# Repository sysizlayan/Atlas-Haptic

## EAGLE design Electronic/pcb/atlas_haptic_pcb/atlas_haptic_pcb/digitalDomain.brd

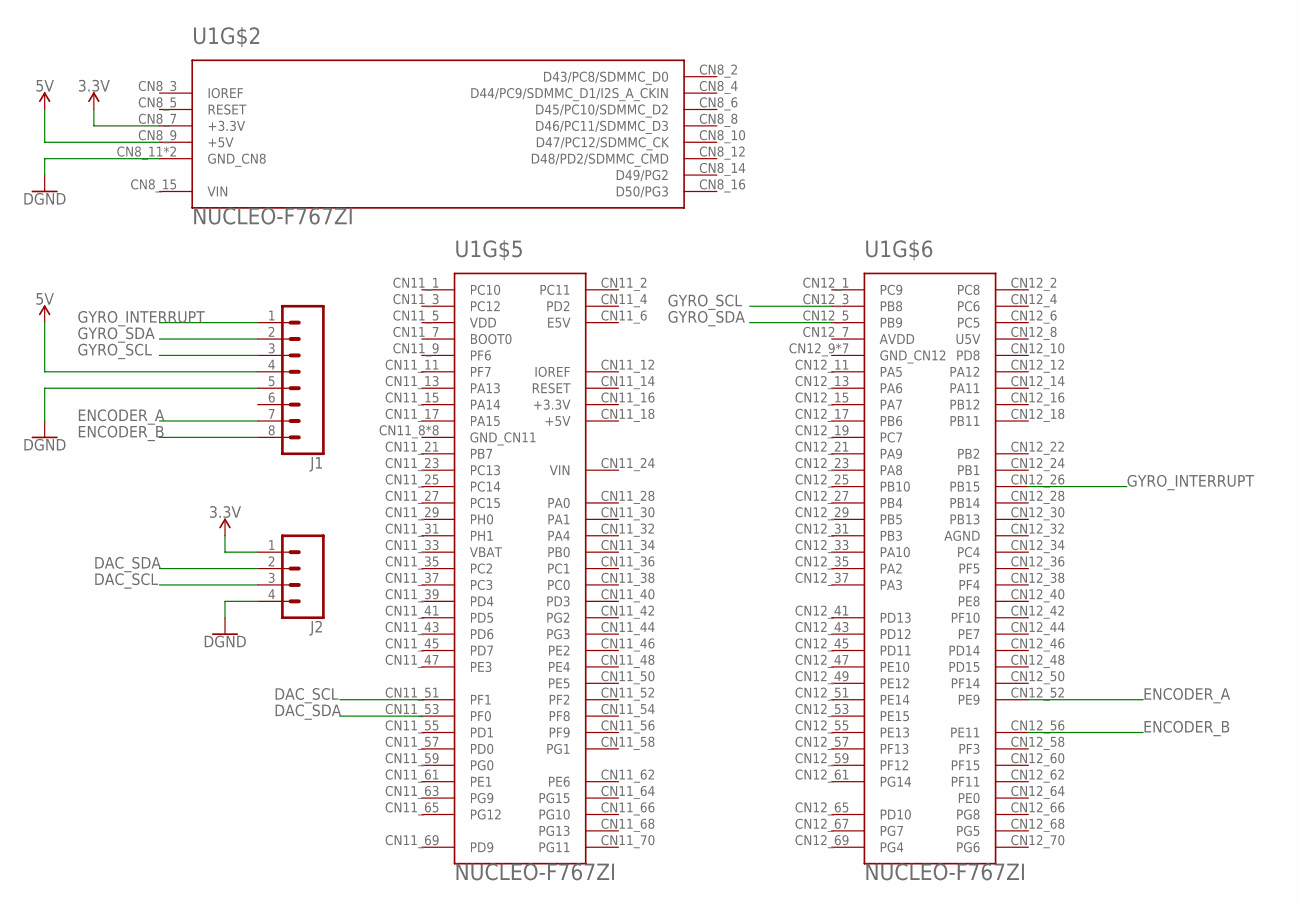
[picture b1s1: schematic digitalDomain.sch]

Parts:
J1: CONN_08LONGPADS; 1X08_LONGPADS
J2: CONN_04LONGPADS; 1X04_LONGPADS
U1: NUCLEO-F767ZI; MODULE_NUCLEO-F429ZI

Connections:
3.3V: J2.1, U1.CN8_7 (+3.3V)
5V: J1.4, U1.CN8_9 (+5V)
DAC_SCL: J2.3, U1.CN11_51 (PF1)
DAC_SDA: J2.2, U1.CN11_53 (PF0)
ENCODER_A: J1.7, U1.CN12_52 (PE9)
ENCODER_B: J1.8, U1.CN12_56 (PE11)
GND: J1.5, J2.4, U1.CN8_11 (GND_CN8), U1.CN8_13 (GND_CN8)
GYRO_INTERRUPT: J1.1, U1.CN12_26 (PB15)
GYRO_SCL: J1.3, U1.CN12_3 (PB8)
GYRO_SDA: J1.2, U1.CN12_5 (PB9)

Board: 2 copper layers, 3 parts (0 on the bottom side), 10 nets, no tracks yet.

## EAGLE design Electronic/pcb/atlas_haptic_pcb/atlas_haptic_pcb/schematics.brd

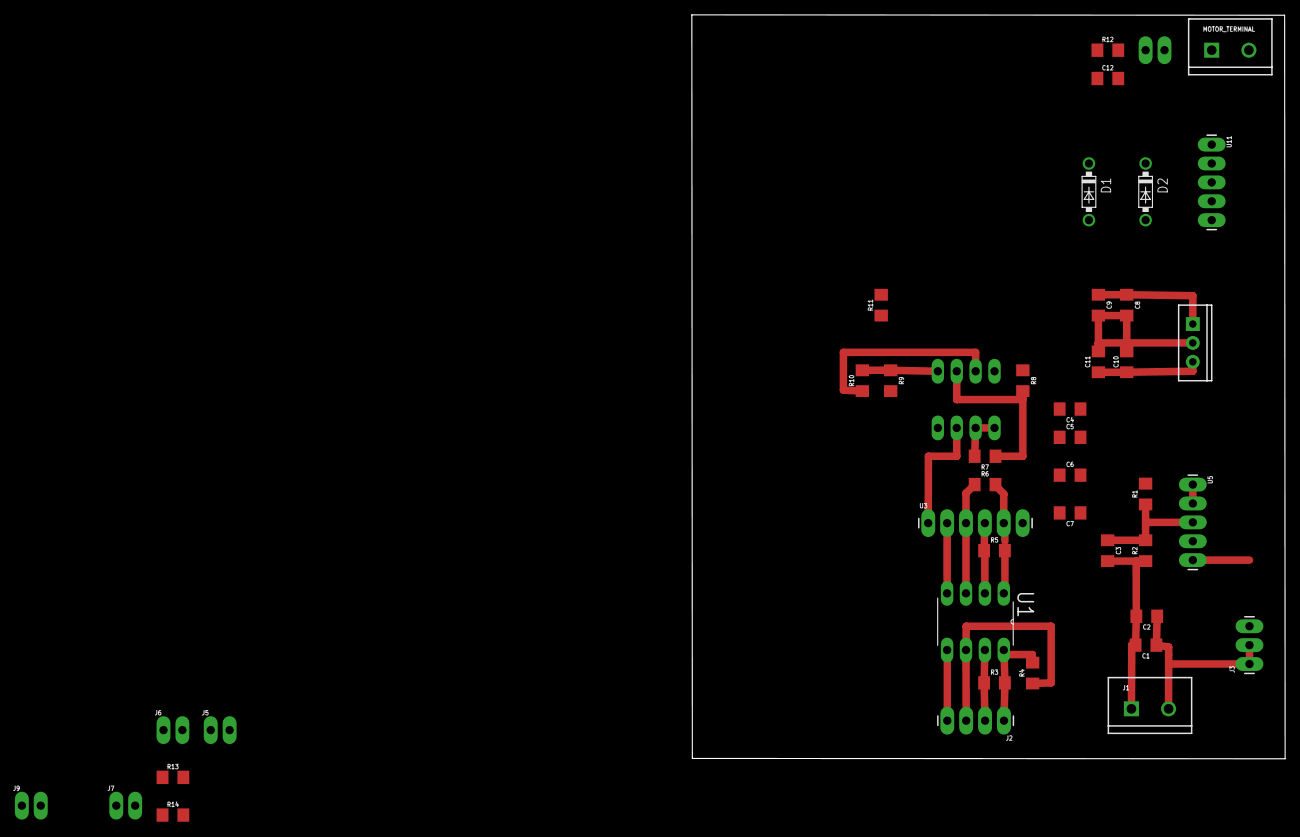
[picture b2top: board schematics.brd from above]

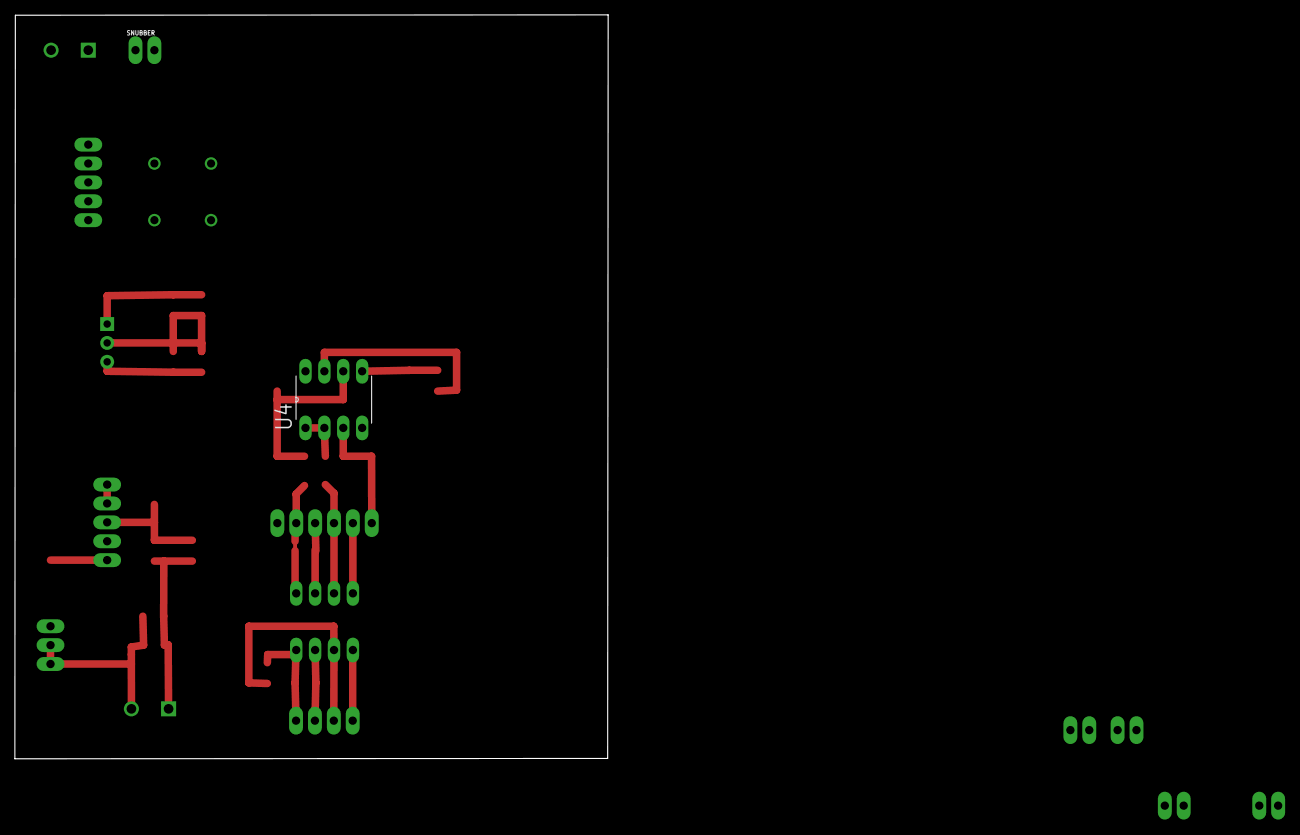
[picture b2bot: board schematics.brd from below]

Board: 2 copper layers, 79.8 x 100.0 mm, 43 parts (2 on the bottom side), 24 nets.

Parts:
C1, C8, C10: 1.0uF; 1206
C2, C3, C4, C6, C9, C11: 100nF; 1206
C5, C7: 1uF; 1206
C12: 1n; 1206
D1, D2: 1N5819-B; DO41-7.6
J1: SCREWTERMINAL-5MM-2
J2: 1X04_LONGPADS
J3: 1X03_LONGPADS
J5, J6, J7, J9: Jumper; 1X02_LONGPADS
MOTOR_TERMINAL: SCREWTERMINAL-5MM-2
R1, R2, R7: 1K; 1206
R3, R4, R5, R6: 1k; 1206
R8, R9, R10: 2K; 1206
R11: 0R01; 1206
R12: 10; 1206
R13: 0R1; 1206
R14: 1R0; 1206
SNUBBER: Jumper; 1X02_LONGPADS
U1: ISO1541; DIP254P762X508-8
U2: TO220-IGO
U3: MCP4725; 1X06_LONGPADS
U4: LM833N; DIP254P762X508-8
U5, U11: OPA549; 1X05_LONGPADS

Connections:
5V: C10.1, C11.1, R5.2, R6.2, R9.2, U1.1, U2.OUT, U3.5
BIASED_VOLTAGE: U3.1, U4.3
DAC_SCL: R6.1, U1.3, U3.3
DAC_SDA: R5.1, U1.2, U3.4
GND: C4.1, C5.2, C6.2, C7.1, C8.2, C9.2, C10.2, C11.2, C12.2, D1.A, D2.C, R8.1, R11.1, R13.1, R14.1, U1.4, U2.GND, U3.2, U3.6, U5.1, U5.2
GND-ISO: J2.4, U1.5
unnamed: C3.1, R1.1, R2.2, U5.3
unnamed: R12.2, SNUBBER.2
unnamed: J2.2, R3.1, U1.7
unnamed: J2.3, R4.1, U1.6
unnamed: R7.2, U4.1, U4.2
unnamed: R7.1, R8.2, U4.6
unnamed: R9.1, R10.2, U4.5
unnamed: MOTOR_TERMINAL.1, SNUBBER.1, U11.1
unnamed: C12.1, R12.1
unnamed: J7.1, J9.1, R14.2
unnamed: J5.2, J6.2, J7.2, J9.2, MOTOR_TERMINAL.2, U11.2
unnamed: J5.1, R13.2
unnamed: J6.1, R11.2
UNBIASED_VOLTAGE: R10.1, U4.7, U11.3
VCC-ISO: J2.1, R3.2, R4.2, U1.8
VDD: C5.1, C6.1, D1.C, U4.8, U11.5
VNEG: C1.2, C2.2, C3.2, C4.2, C7.2, D2.A, J1.1, R2.1, U4.4, U11.4
VPOS: C1.1, C2.1, C8.1, C9.1, J1.2, J3.1, J3.2, J3.3, R1.2, U2.IN

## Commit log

2018-03-24 init
2018-03-24 Uart is added
2018-03-24 Led and buttons are implemented
2018-03-24 QEI, buttons, leds and time module is initialized.
2018-03-25 global headers are initialized
2018-03-25 Everything is set, system will be tested after cabling
2018-03-25 Rom functions are disabled
2018-03-25 Folders contaitning software are moved to the software folder
2018-03-26 Return to tm4c123gh6pm, i2c has some errors on tm4c129.
2018-03-27 code cleaning
2018-03-28 BUGFIX: Time value bug is solved.
2018-03-28 MCP4725 DAC is implemented.
2018-04-15 after TORK
2018-04-15 Driver simulations
2018-04-15 simulation is done, production
2018-04-17 stm32_trial
2018-04-18 OPA569 is tested, rail-torail opamp will be chosen for current sensing
2018-04-18 folder re-organizing
2018-04-18 schematic is added
2018-04-18 In the circuit, OPA569 and INA193 will be used.
2018-04-18 stm update
2018-04-23 current driver
2018-05-13 DAC is implemented and tested.
2018-05-13 stm32_f746zg implementation has begun
2018-05-13 headers are copied
2018-05-14 Target tracking is implemented
2018-05-15 Simulation is tested, errors are corrected.
2018-05-17 GUI is seperated into 2, circular and linear
2018-05-17 Circular tracking is implemented and tested.
2018-05-19 Time is corrected. Micros function is faulty. Gyro clock is the main clock source now.
2018-05-20 Measurements are recorded.
2018-06-08 STM32 test
2018-09-19 Mutiple sine calculations
2018-09-19 stm32 revized
2018-09-23 T gilter paper is added
2018-09-25 STM32 board now can take the measurements, do the calculations and then print the results back to computer.
    Floating point array which will contain the target position data are also written globally, currently 40KB of free memory is available.
2018-09-28 Kalman filter error has been fixed.
    Previous value of the position has not been saved, it is fixed. Now, time update is being processed.
2018-09-28 Some test codes for matlab
2018-09-29 DAC implementation for STM32 processors.
2018-09-29 DAC functions are written, states are moved into main
2018-09-30 Somenew Kalman model tests
2018-09-30 Measurements are taken. 2 types of kalman code is ported according to these masurements
2018-09-30 Figures and data files are added.
2018-10-01 Unnecessary files and folders are added
2018-10-04 Accelereration estimating kalman filter is implemented, optimization will be done later.
2018-10-05 Ethics forlder is added, application form has been filled.
2018-10-10 Some kalman tests
2018-10-21 Sine/cosine calculation method is changed.
2018-10-21 Before json parsing implementation
    Configuration will be loaded from json coming from serial port.
2018-10-24 Parameter parsing is waiting.
2018-10-26 EM test initialization
2018-10-29 Kalman smoother or 1st order kalman equations
2018-10-29 Expectation maximization for 1st order kalman model is implemented. New models will be added.
2018-10-30 Constant velocity model is added, implementation will continue.
2018-11-01 Json parsing for experiment config is implemented.
    Functions periods and experiment configuration is tested.
    To add new variables to configuration, you need to write a code to main loop.
    Experiment has 5 states:
    The device
    1) Starts,
    2) Does the calibration,
2018-11-01 Configuration parsing is moved to parseConfig.c file.
2018-11-01 Measurement concatanation script is added. EM algorithm is tested with that.
2018-11-01 Some performance metrics are added.
2018-11-01 GPIO button configuration is implemented and force gain is calibrated and tested.
2018-11-03 New GUI is implemented. Experiment sequence will be implemented later on that GUI.
2018-11-06 Json editor GUI is implemented.
2018-11-08 Json config editor is implemented, imported to plot script and tested.
2018-11-11 Pygame functions are changed with OpenGl functions to get harware accelerartion.
2018-11-11 Screen is optimized for 240Hz
2018-11-11 Initialization is optimized.
2018-11-13 Optimization for PC in the laboratory is done!
2018-11-14 Requirements are added.
2018-11-16 GUI is working fullscreen now.
2018-11-25 EM implemented up to Q
2018-11-25 EM for encoder only model is implemented.
2018-12-08 Encoder only estimation method is enhanced, works better now.
2018-12-10 2nd order kalman with velocity measurement from encoder is implemented and optimized.
    2nd order model with gyro as input will be implemented too.
2018-12-10 Gyro input kalman model is written and tested. Sampling decreaser will be written again.
2018-12-11 Acceleration estimating model is implemented.
2018-12-15 Commit for latex interpreted figures
2018-12-15 2nd order kalman filter is finished. Works fine, figures will be taken.
2018-12-15 Encoder only kalman model is fit. Results are saved.
2018-12-15 Acceleration estimating kalman model is tested but needs more work.
2018-12-16 Sample decreaser is implemented and tested. Works well.
    Last code before figure generation. Sample decreaser implemented using smoothed output of 1st order gyro input kalman model. First smoothed data is interpolated by 100, resampled with given CPR value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
2018-12-16 Low resolution encoder is optimized and results are saved. Figures are plotted.
    Low resolution encoder scripts are written. Q and R values are optimized using EM accordingly. Resulting values are saved and figures are plotted as PNG files.
    PDF versions of the figures will be drawn and kalman part of the thesis will be written with them.
2019-02-17 Circurit diagram for the PCB is drawen. Some meaurements are taken an phase lag issue is not observed.
    The effect of the snubber circuit is easily observed.
2019-02-23 Figure of the circuit is updated. Mechanical part is revised.
2019-03-08 Current controller is implemented.
2019-03-23 PDF folder is deleted
2019-03-23 Some old embedded codes are cleaned
2019-03-23 Electronic simulations are added.
2019-03-25 2dof haptic drawings were added
2019-03-31 Comparison structures are added.
2019-04-01 comparison data is added.
2019-04-10 drawings were updated for sigma profile
2019-04-11 small fixes
2019-04-20 CDF and PDF code is added. Acemp2019 is submitted.
2019-04-23 Downsampling is corrected.
2019-04-27 Distribution test is updated, noise calculator is added.
2019-05-06 Distribution tests
2019-05-06 fixed untracked files
2019-05-27 Digital domain schematics is added.
2019-05-27 Digital domain contd.
2019-05-28 Some additions
2019-06-01 contd PWM controller
2019-06-01 PWM schematic contd.
2019-06-05 PWM torque controller is added.
2019-08-27 2dof haptic some parts edited

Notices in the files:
parts and their libraries:
SparkFun-Connectors: Licensing: Creative Commons ShareAlike 4.0 International - https://creativecommons.org/licenses/by-sa/4.0
